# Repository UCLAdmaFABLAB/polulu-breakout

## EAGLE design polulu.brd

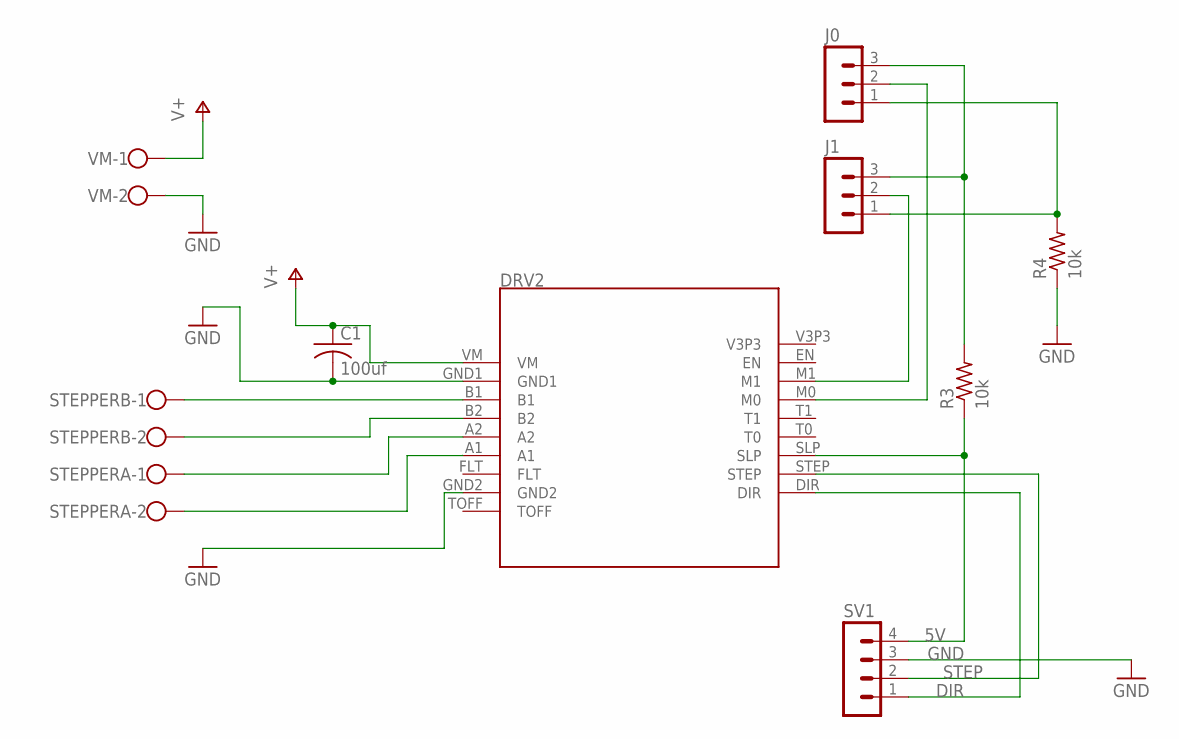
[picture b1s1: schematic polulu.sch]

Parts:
C1: 100uf; C025-024X044
DRV2: DRV8880
J0, J1: MA03-1
R3, R4: 10k; 0204/7
STEPPERA: W237-102
STEPPERB: W237-102
SV1: MA04-1
VM: W237-102

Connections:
5V: DRV2.SLP, R3.1, SV1.4
DIR: DRV2.DIR, SV1.1
GND: C1.2, DRV2.GND1, DRV2.GND2, R4.1, SV1.3, VM.2
unnamed: DRV2.A2, STEPPERA.1
unnamed: DRV2.A1, STEPPERA.2
unnamed: DRV2.M1, J1.2
unnamed: DRV2.M0, J0.2
unnamed: J0.3, J1.3, R3.2
unnamed: J0.1, J1.1, R4.2
STEP: DRV2.STEP, SV1.2
STEPPERB1: DRV2.B1, STEPPERB.1
STEPPERB2: DRV2.B2, STEPPERB.2
V+: C1.1, DRV2.VM, VM.1

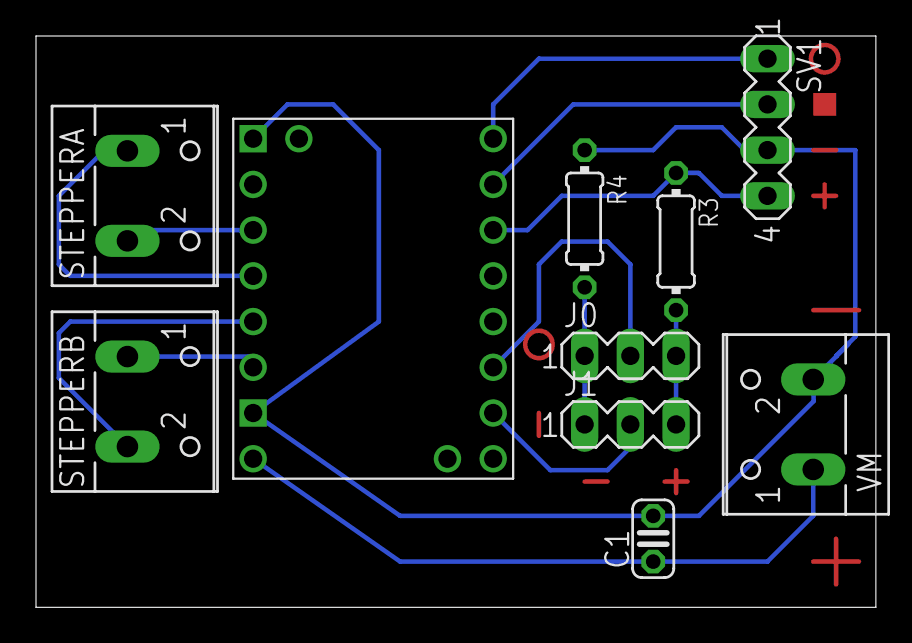
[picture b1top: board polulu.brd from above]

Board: 2 copper layers, 46.7 x 31.7 mm, 10 parts (0 on the bottom side), 13 nets.

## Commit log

2019-12-04 working DRV8880 board
